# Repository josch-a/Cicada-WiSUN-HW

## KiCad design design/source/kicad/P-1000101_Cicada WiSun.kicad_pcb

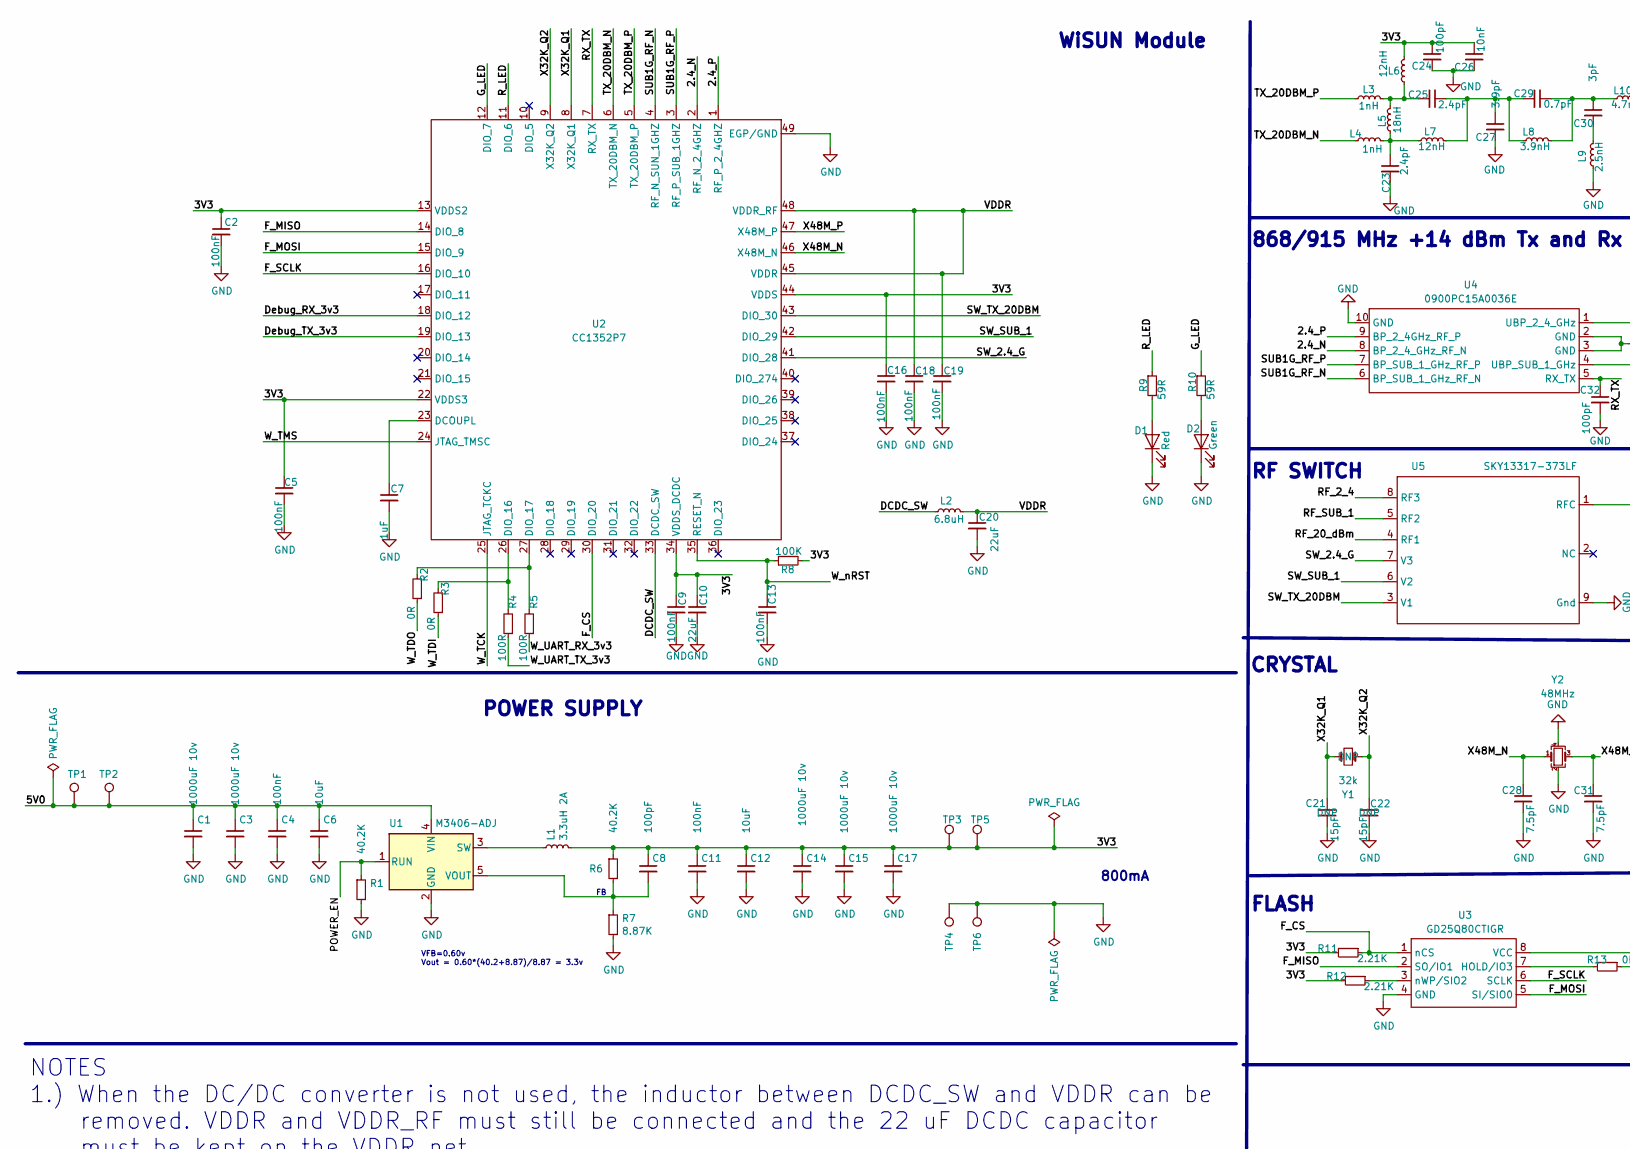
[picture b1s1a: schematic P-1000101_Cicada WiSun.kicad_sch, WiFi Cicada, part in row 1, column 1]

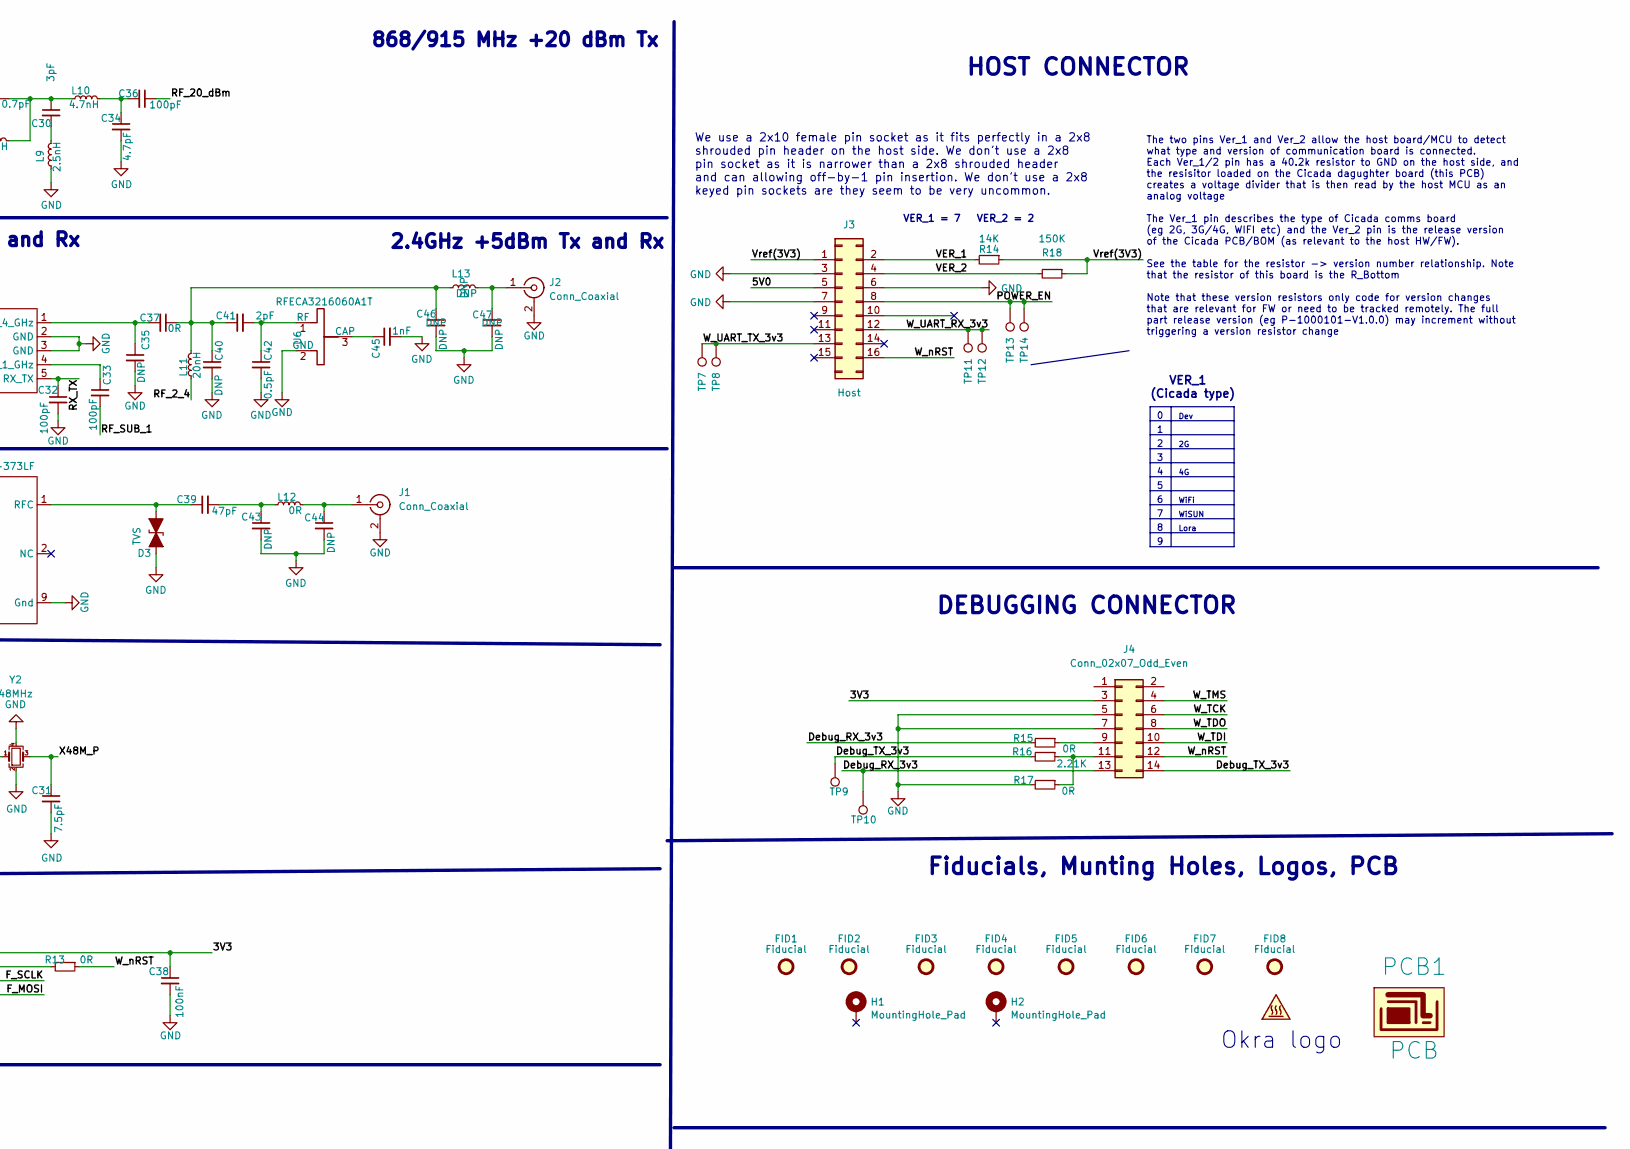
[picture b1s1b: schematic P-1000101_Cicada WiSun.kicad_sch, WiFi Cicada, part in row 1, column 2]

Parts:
C1, C3, C14, C15, C17: 1000uF 10v; CP_Radial_D8.0mm_P3.50mm; MPN GR108M010F12RR0VL4FP0
C2, C5, C9, C11, C13, C16, C18, C19, C38: 100nF; C_0402_1005Metric; MPN CC0402KRX5R7BB104
C4: 100nF; C_0603_1608Metric; MPN CC0603JRX7R7BB104
C6, C12: 10uF; C_0402_1005Metric; MPN CC0402MRX5R6BB106
C7: 1uF; C_0402_1005Metric; MPN CC0402KPX5R7BB105
C8: 100pF; C_0603_1608Metric; MPN CC0603GPNPO9BN101
C10, C20: 22uF; C_0603_1608Metric; MPN CL10A226MO7JZNC
C21, C22: 15pF; C_0402_1005Metric; MPN CC0402JRNPO7BN150
C23, C25: 2.4pF; C_0402_1005Metric; MPN CC0402CRNPO9BN2R4
C24, C32, C33, C36: 100pF; C_0402_1005Metric; MPN CC0402JRNPO9BN101
C26: 10nF; C_0402_1005Metric; MPN CC0402KRX5R8BB103
C27: 3.9pF; C_0402_1005Metric; MPN CQ0402ARNPO9BN3R9
C28, C31: 7.5pF; C_0402_1005Metric; MPN CQ0402BRNPO9BN7R5
C29: 0.7pF; C_0402_1005Metric; MPN CC0402CRNPO9BNR70
C30: 3pF; C_0402_1005Metric; MPN CC0402BRNPO9BN3R0
C34: 4.7pF; C_0402_1005Metric; MPN CC0402BRNPO9BN4R7
C35, C40, C43, C44, C46, C47: DNP; C_0402_1005Metric; MPN DNP
C37: 0R; C_0402_1005Metric; MPN RC0402JR-070RL
C39: 47pF; C_0402_1005Metric; MPN CC0402JRNPO9BN470
C41: 2pF; C_0402_1005Metric; MPN AC0402CRNPO9BN2R0
C42: 0.5pF; C_0402_1005Metric; MPN CQ0402ARNPO9BNR50
C45: 1nF; C_0402_1005Metric; MPN CC0402KRX7R9BB102
D1: Red; LED_0402_1005Metric; MPN 16-213SURC/S530-A3/TR8
D2: Green; LED_0402_1005Metric; MPN 16-213/G6C-AK2L2VY/3T
D3: TVS; X1SON; MPN TPD1E0B04DPYR
FID1, FID2, FID3, FID4, FID5, FID6, FID7, FID8: Fiducial; Fiducial_0.5mm_Mask1mm; MPN DNP
H1, H2: MountingHole_Pad; MountingHole_3.2mm_M3_ISO14580_Pad; MPN DNP
J1, J2: Conn_Coaxial; U.FL_Molex_MCRF_73412-0110_Vertical; MPN U.FL-R-SMT-1(80)
J3: Host; PinSocket_2x08_P2.54mm_Vertical_padded; MPN C30867
J4: Conn_02x07_Odd_Even; Pin_Header_2x07_P1.27mm_Vertical_SMT; MPN X1270WVS-2x07B-6TV01
L1: 3.3uH 2A; L_4030_Handsoldering; MPN FPI0403F-3R3M
L2: 6.8uH; L_0805_2012Metric; MPN FCI2012F-6R8K
L3, L4: 1nH; L_0402_1005Metric; MPN SDCL1005C1N0STDF
L5: 18nH; L_0402_1005Metric; MPN MWSD1005C18NGT
L6, L7: 12nH; L_0402_1005Metric; MPN SDCL1005C12NJTDF
L8: 3.9nH; L_0402_1005Metric; MPN SDCL1005C3N9STDF
L9: 2.5nH; L_0402_1005Metric; MPN HQ1005C2N5ST
L10: 4.7nH; L_0402_1005Metric; MPN SDCL1005C4N7STDFM01
L11: 20nH; C_0402_1005Metric; MPN SDCL1005C20NJTDF
L12: 0R; L_0402_1005Metric; MPN RC0402JR-070RL
L13: DNP; L_0402_1005Metric; MPN DNP
LOGO1: SYM_Hot_Small; okra_logo_s; MPN DNP
PCB1: PCB; MPN DNP
R1, R6: 40.2K; R_0603_1608Metric; MPN RC0603FR-0740K2L
R2, R3, R13, R15, R17: 0R; R_0402_1005Metric; MPN RC0402JR-070RL
R4, R5: 100R; R_0402_1005Metric; MPN RC0402FR-07100KL
R7: 8.87K; R_0603_1608Metric; MPN RC0603FR-078K87L
R8: 100K; R_0402_1005Metric; MPN RC0402FR-07100KL
R9, R10: 59R; R_0402_1005Metric; MPN AC0402FR-0759RL
R11, R12: 2.21K; R_0402_1005Metric; MPN RC0402FR-072K21L
R14: 14K; R_0603_1608Metric; MPN AR0603FR-0714KL
R16: 2.21K; R_0402_1005Metric; MPN RC0402JR-070RL
R18: 150K; R_0603_1608Metric; MPN RC0603FR-07150KL
TP1, TP2: 5v0; TestPoint_Pad_D1.5mm; MPN DNP
TP3, TP5, TP6: 3v3; TestPoint_Pad_D1.5mm; MPN DNP
TP4: GND; TestPoint_Pad_D1.5mm; MPN DNP
TP7, TP8: Data_Tx; TestPoint_Pad_D1.5mm; MPN DNP
TP9: Debug_Tx; TestPoint_Pad_D1.5mm; MPN DNP
TP10: Debug_Rx; TestPoint_Pad_D1.5mm; MPN DNP
TP11, TP12: Data_Rx; TestPoint_Pad_D1.5mm; MPN DNP
TP13, TP14: PW_EN; TestPoint_Pad_D1.5mm; MPN DNP
U1: M3406-ADJ; TSOT-23-5; MPN M3406-ADJ
U2: CC1352P7; MPN CC1352P74T0RGZR
U3: GD25Q80CTIGR; MPN GD25Q80CTIGR
U4: 0900PC15A0036E; MPN 0900PC15A0036E
U5: SKY13317-373LF; MPN SKY13317-373LF
U6: RFECA3216060A1T; MPN RFECA3216060A1T
Y1: 32k; Crystal_SMD_2012-2Pin_2.0x1.2mm; MPN ECS-.327-7-12-C-TR
Y2: 48MHz; Crystal_SMD_2016-4Pin_2.0x1.6mm; MPN NX2016SA-48M-EXS00A-CS05517

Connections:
/2.4_N: U2.2 (RF_N_2_4GHZ), U4.8 (BP_2_4_GHz_RF_N)
/2.4_P: U2.1 (RF_P_2_4GHZ), U4.9 (BP_2_4GHz_RF_P)
/3V3: C2.1, C5.1, C8.1, C9.1, C10.1, C11.1, C12.1, C14.1, C15.1, C16.1, C17.1, C24.1, C26.1, C38.1, J4.3, L1.2, L6.2, R6.1, R8.2, R11.2, R12.2, TP3.1, TP5.1, U2.13 (VDDS2), U2.22 (VDDS3), U2.34 (VDDS_DCDC), U2.44 (VDDS), U3.8 (VCC)
/5V0: C1.1, C3.1, C4.1, C6.1, J3.5, TP1.1, TP2.1, U1.4 (VIN)
/DCDC_SW: L2.1, U2.33 (DCDC_SW)
/Debug_RX_3v3: J4.13, R15.2, TP10.1, U2.18 (DIO_12)
/Debug_TX_3v3: J4.14, R16.2, TP9.1, U2.19 (DIO_13)
/F_CS: R11.1, U2.30 (DIO_20), U3.1 (nCS)
/F_MISO: U2.14 (DIO_8), U3.2 (SO/IO1)
/F_MOSI: U2.15 (DIO_9), U3.5 (SI/SIO0)
/F_SCLK: U2.16 (DIO_10), U3.6 (SCLK)
/G_LED: R10.1, U2.12 (DIO_7)
/POWER_EN: J3.8, R1.1, TP13.1, TP14.1, U1.1 (RUN)
/RF_2_4: L11.1, U5.8 (RF3)
/RF_20_dBm: C36.1, U5.4 (RF1)
/RF_SUB_1: C33.2, U5.5 (RF2)
/RX_TX: C32.1, U2.7 (RX_TX), U4.5 (RX_TX)
/R_LED: R9.1, U2.11 (DIO_6)
/SUB1G_RF_N: U2.4 (RF_N_SUN_1GHZ), U4.6 (BP_SUB_1_GHz_RF_N)
/SUB1G_RF_P: U2.3 (RF_P_SUB_1GHZ), U4.7 (BP_SUB_1_GHz_RF_P)
/SW_2.4_G: U2.41 (DIO_28), U5.7 (V3)
/SW_SUB_1: U2.42 (DIO_29), U5.6 (V2)
/SW_TX_20DBM: U2.43 (DIO_30), U5.3 (V1)
/TX_20DBM_N: L4.1, U2.6 (TX_20DBM_N)
/TX_20DBM_P: L3.1, U2.5 (TX_20DBM_P)
/VDDR: C18.1, C19.1, C20.1, L2.2, U2.45 (VDDR), U2.48 (VDDR_RF)
/VER_1: J3.2, R14.2
/VER_2: J3.4, R18.2
/Vref(3V3): J3.1, R14.1, R18.1
/W_TCK: J4.6, U2.25 (JTAG_TCKC)
/W_TDI: J4.10, R3.1
/W_TDO: J4.8, R2.1
/W_TMS: J4.4, U2.24 (JTAG_TMSC)
/W_UART_RX_3v3: J3.12, R5.1, TP11.1, TP12.1
/W_UART_TX_3v3: J3.13, R4.1, TP7.1, TP8.1
/W_nRST: C13.1, J3.16, J4.12, R8.1, R13.1, U2.35 (RESET_N)
/X32K_Q1: C21.1, U2.8 (X32K_Q1), Y1.2
/X32K_Q2: C22.1, U2.9 (X32K_Q2), Y1.1
/X48M_N: C28.1, U2.46 (X48M_N), Y2.1
/X48M_P: C31.1, U2.47 (X48M_P), Y2.3
GND: C1.2, C2.2, C3.2, C4.2, C5.2, C6.2, C7.2, C9.2, C10.2, C11.2, C12.2, C13.2, C14.2, C15.2, C16.2, C17.2, C18.2, C19.2, C20.2, C21.2, C22.2, C23.2, C24.2, C26.2, C27.2, C28.2, C31.2, C32.2, C34.2, C35.2, C38.2, C40.2, C42.2, C43.2, C44.2, C45.2, C46.2, C47.2, D1.1 (K), D2.1 (K), D3.2 (A2), J1.2 (Ext), J2.2 (Ext), J3.3, J3.6, J3.7, J4.5, J4.7, L9.1, R1.2, R7.2, R17.2, TP4.1, TP6.1, U1.2 (GND), U2.49 (EGP/GND), U3.4 (GND), U4.2 (GND), U4.3 (GND), U4.10 (GND), U5.9 (Gnd), U6.2 (GND), Y2.2, Y2.4
unnamed: C23.1, L4.2, L5.1, L7.1
unnamed: C25.1, C27.1, C29.2, L7.2, L8.1
unnamed: C25.2, L3.2, L5.2, L6.1
unnamed: C29.1, C30.1, L8.2, L10.1
unnamed: C30.2, L9.2
unnamed: C34.1, C36.2, L10.2
unnamed: C37.1, C40.1, C41.1, C46.1, L11.2, L13.1
unnamed: C39.2, C43.1, L12.1
unnamed: D1.2 (A), R9.2
unnamed: D2.2 (A), R10.2
unnamed: C39.1, D3.1 (A1), U5.1 (RFC)
unnamed: C44.1, J1.1 (In), L12.2
unnamed: C47.1, J2.1 (In), L13.2
unnamed: J4.9, R15.1
unnamed: J4.11, R16.1, R17.1
unnamed: L1.1, U1.3 (SW)
unnamed: C8.2, R6.2, R7.1, U1.5 (VOUT)
unnamed: C7.1, U2.23 (DCOUPL)
unnamed: R3.2, R4.2, U2.26 (DIO_16)
unnamed: R2.2, R5.2, U2.27 (DIO_17)
unnamed: R13.2, U3.7 (HOLD/IO3)
unnamed: R12.1, U3.3 (nWP/SIO2)
unnamed: C35.1, C37.2, U4.1 (UBP_2_4_GHz)
unnamed: C33.1, U4.4 (UBP_SUB_1_GHz)
unnamed: C45.1, U6.3 (CAP)
unnamed: C41.2, C42.1, U6.1 (RF)

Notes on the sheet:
VER_1 = 7
HOST CONNECTOR
NOTES 1.) When the DC/DC converter is not used, the inductor between DCDC_SW and VDDR can be removed. VDDR and VDDR_RF must still be connected and the 22 uF DCDC capacitor must be kept on the VDDR net. 2.) EGP is the only ground connection for the device. Good electrical connection to device ground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
2.4GHz +5dBm Tx and Rx
CRYSTAL
Lora
POWER SUPPLY
WiSUN Module
VER_1 (Cicada type)
DEBUGGING CONNECTOR
VER_2 = 2
Okra logo
WiFi
RF SWITCH
Fiducials, Munting Holes, Logos, PCB
FLASH
VFB=0.60v Vout = 0.60*(40.2+8.87)/8.87 = 3.3v
The two pins Ver_1 and Ver_2 allow the host board/MCU to detect what type and version of communication board is connected. Each Ver_1/2 pin has a 40.2k resistor to GND on the host side, and the resisitor loaded on the Cicada dagughter board (this PCB) creates a voltage divider that is then read by 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
800mA
We use a 2x10 female pin socket as it fits perfectly in a 2x8 shrouded pin header on the host side. We don't use a 2x8 pin socket as it is narrower than a 2x8 shrouded header and can allowing off-by-1 pin insertion. We don't use a 2x8 keyed pin sockets are they seem to be very uncommon.
868/915 MHz +20 dBm Tx
868/915 MHz +14 dBm Tx and Rx
Dev
WiSUN

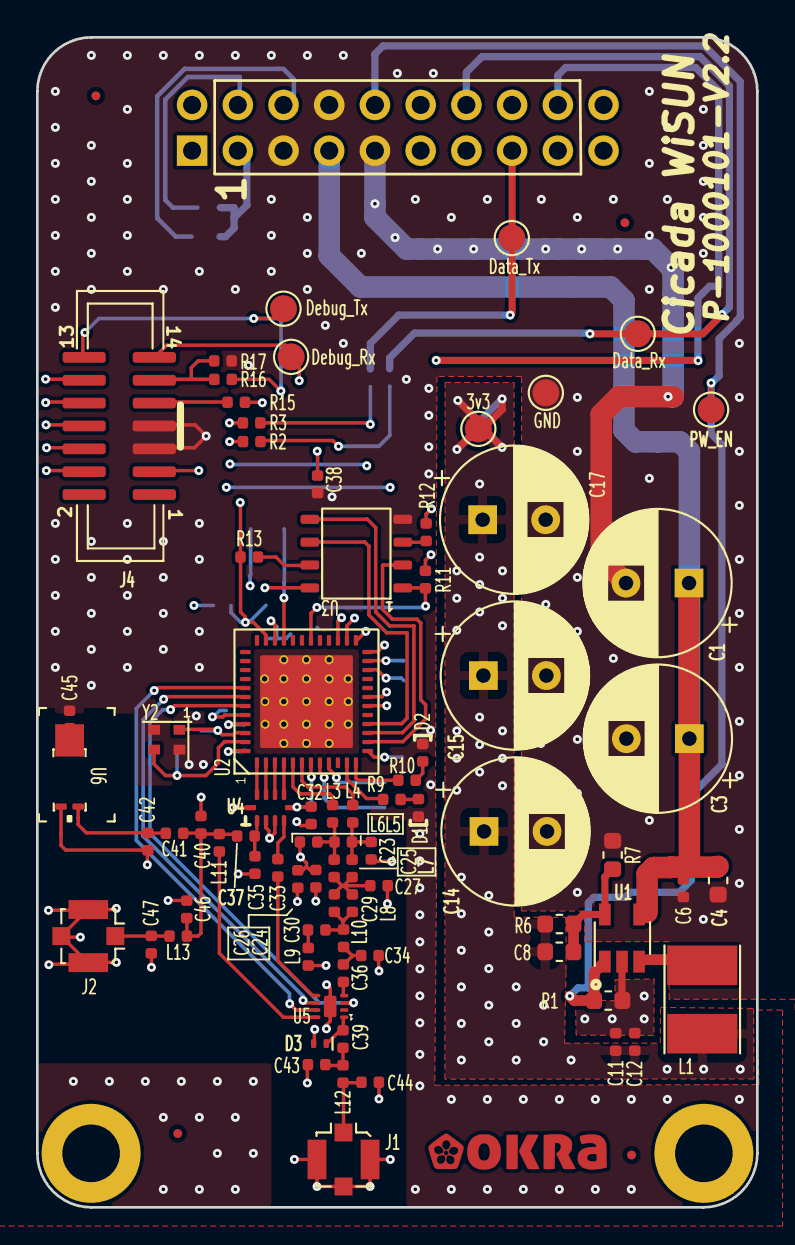
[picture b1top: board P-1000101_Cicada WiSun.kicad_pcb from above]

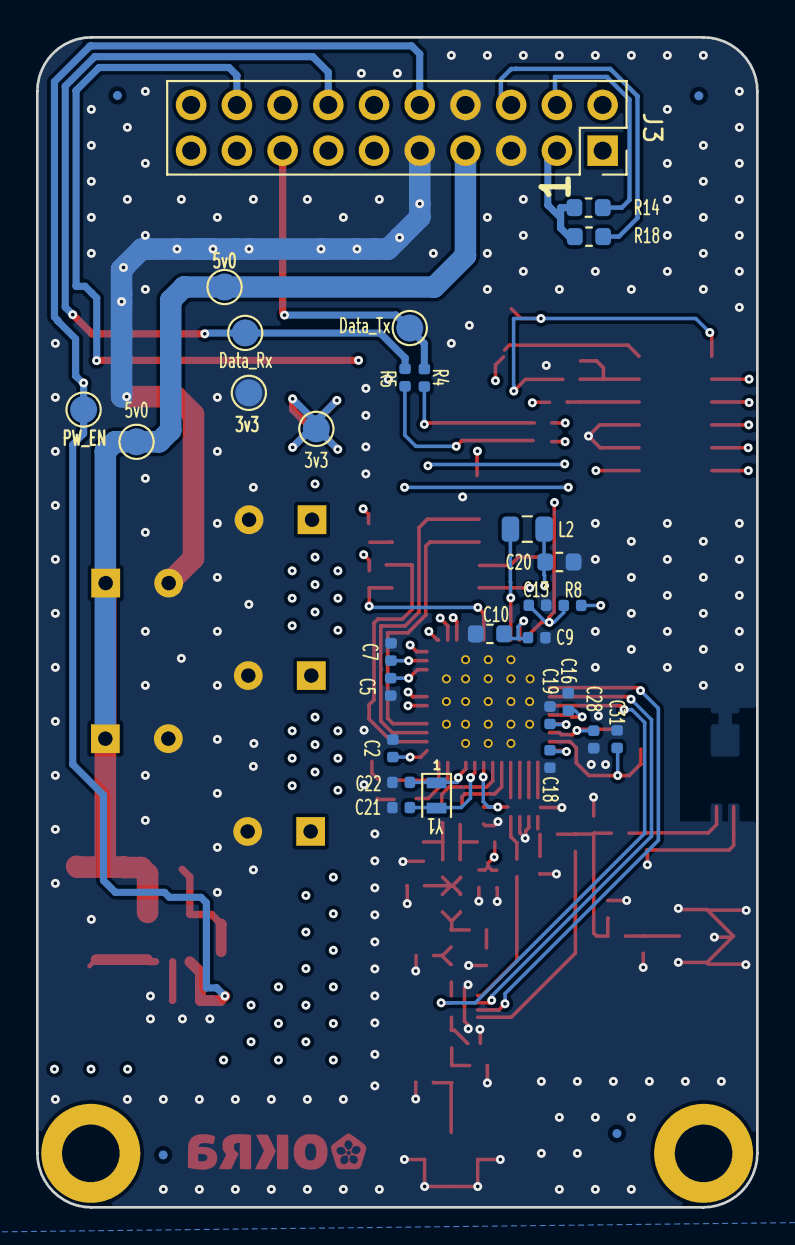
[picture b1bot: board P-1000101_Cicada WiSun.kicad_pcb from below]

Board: 4 copper layers, 40.0 x 65.0 mm, 118 parts (33 on the bottom side), 67 nets.

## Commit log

2026-03-27 initial creation
